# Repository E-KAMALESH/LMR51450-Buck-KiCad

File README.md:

# LMR51450-Buck-KiCad
KiCad DC-DC buck converter design using Texas Instruments LMR51450 — 10–35V input, 7.6V/4A output. Includes schematic, PCB layout,BOM,media snapshots.

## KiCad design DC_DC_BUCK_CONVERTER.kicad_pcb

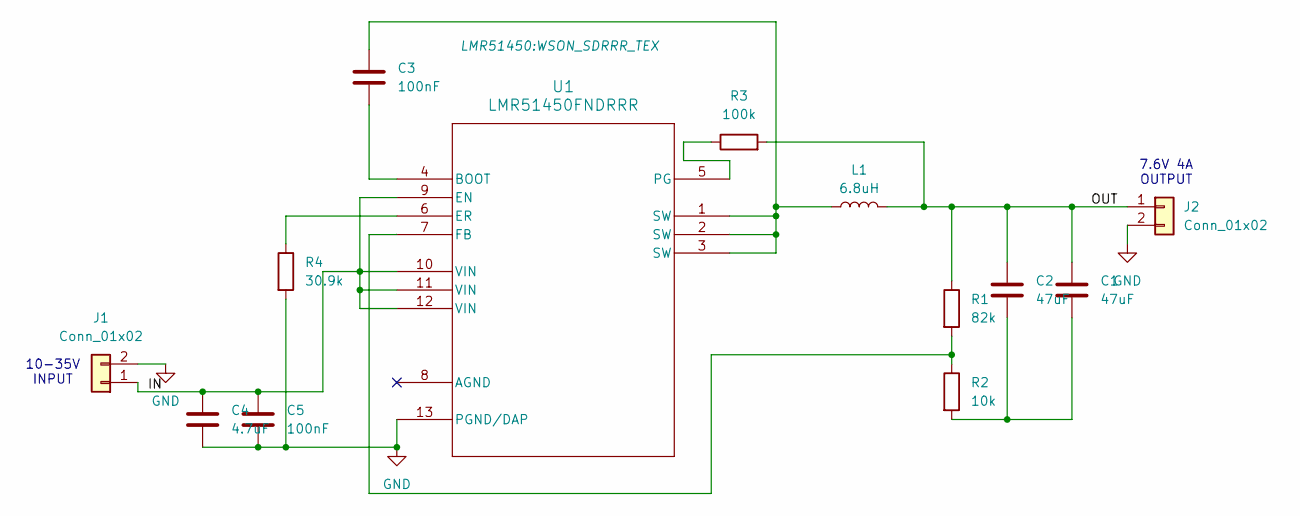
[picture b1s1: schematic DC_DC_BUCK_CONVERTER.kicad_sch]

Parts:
C1, C2: 47uF; C_1206_3216Metric
C3, C5: 100nF; C_0603_1608Metric
C4: 4.7uF; C_1206_3216Metric
J1, J2: Conn_01x02; PinHeader_1x02_P2.54mm_Vertical
L1: 6.8uH; L_7.3x7.3_H3.5
R1: 82k; R_0603_1608Metric
R2: 10k; R_0603_1608Metric
R3: 100k; R_0603_1608Metric
R4: 30.9k; R_0603_1608Metric
U1: LMR51450FNDRRR; WSON_SDRRR_TEX

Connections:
/IN: C4.1, C5.1, J1.1, U1.9 (EN), U1.10 (VIN), U1.11 (VIN), U1.12 (VIN)
/OUT: C1.1, C2.1, J2.1, L1.2, R1.1, R3.2
GND: C4.2, C5.2, J1.2, J2.2, R4.2, U1.13 (PGND/DAP)
unnamed: C1.2, C2.2, R2.2
unnamed: C3.1, L1.1, U1.1 (SW), U1.2 (SW), U1.3 (SW)
unnamed: C3.2, U1.4 (BOOT)
unnamed: R4.1, U1.6 (ER)
unnamed: R1.2, R2.1, U1.7 (FB)
unnamed: R3.1, U1.5 (PG)

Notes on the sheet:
10-35V INPUT
7.6V 4A OUTPUT

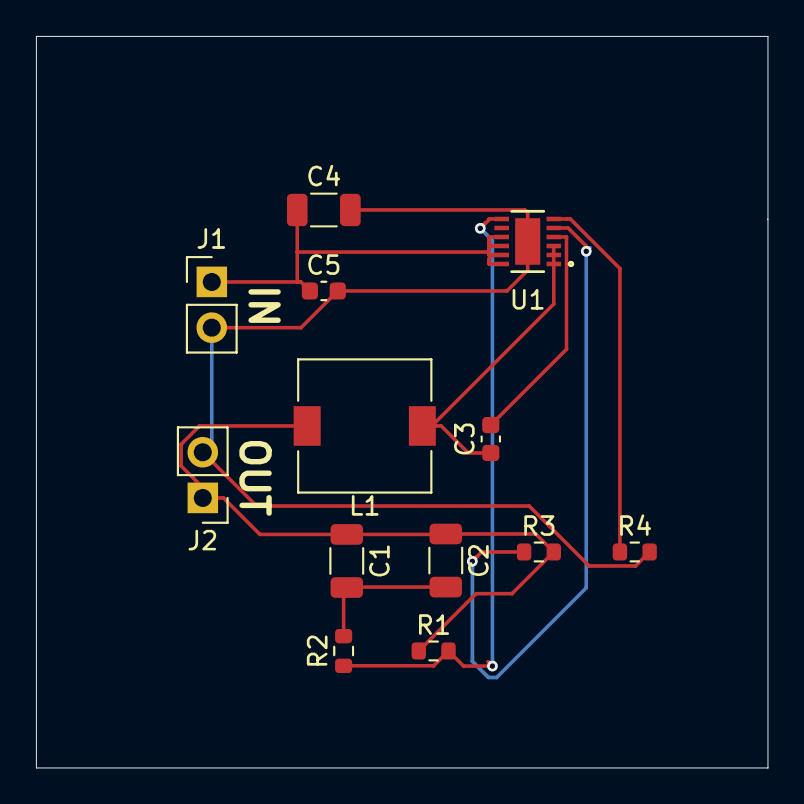
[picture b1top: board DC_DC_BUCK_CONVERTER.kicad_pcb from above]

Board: 2 copper layers, 40.6 x 40.6 mm, 13 parts (0 on the bottom side), 9 nets.

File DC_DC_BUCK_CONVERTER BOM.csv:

"Reference","Qty","Value","DNP","Exclude from BOM","Exclude from Board","Footprint","Datasheet"
"C1,C2","2","47uF","","","","Capacitor_SMD:C_1206_3216Metric","~"
"C3,C5","2","100nF","","","","Capacitor_SMD:C_0603_1608Metric","~"
"C4","1","4.7uF","","","","Capacitor_SMD:C_1206_3216Metric","~"
"J1,J2","2","Conn_01x02","","","","Connector_PinHeader_2.54mm:PinHeader_1x02_P2.54mm_Vertical","~"
"L1","1","6.8uH","","","","Inductor_SMD:L_7.3x7.3_H3.5","~"
"R1","1","82k","","","","Resistor_SMD:R_0603_1608Metric","~"
"R2","1","10k","","","","Resistor_SMD:R_0603_1608Metric","~"
"R3","1","100k","","","","Resistor_SMD:R_0603_1608Metric","~"
"R4","1","30.9k","","","","Resistor_SMD:R_0603_1608Metric","~"
"U1","1","LMR51450FNDRRR","","","","LMR51450:WSON_SDRRR_TEX","https://www.ti.com/lit/gpn/lmr51450"
